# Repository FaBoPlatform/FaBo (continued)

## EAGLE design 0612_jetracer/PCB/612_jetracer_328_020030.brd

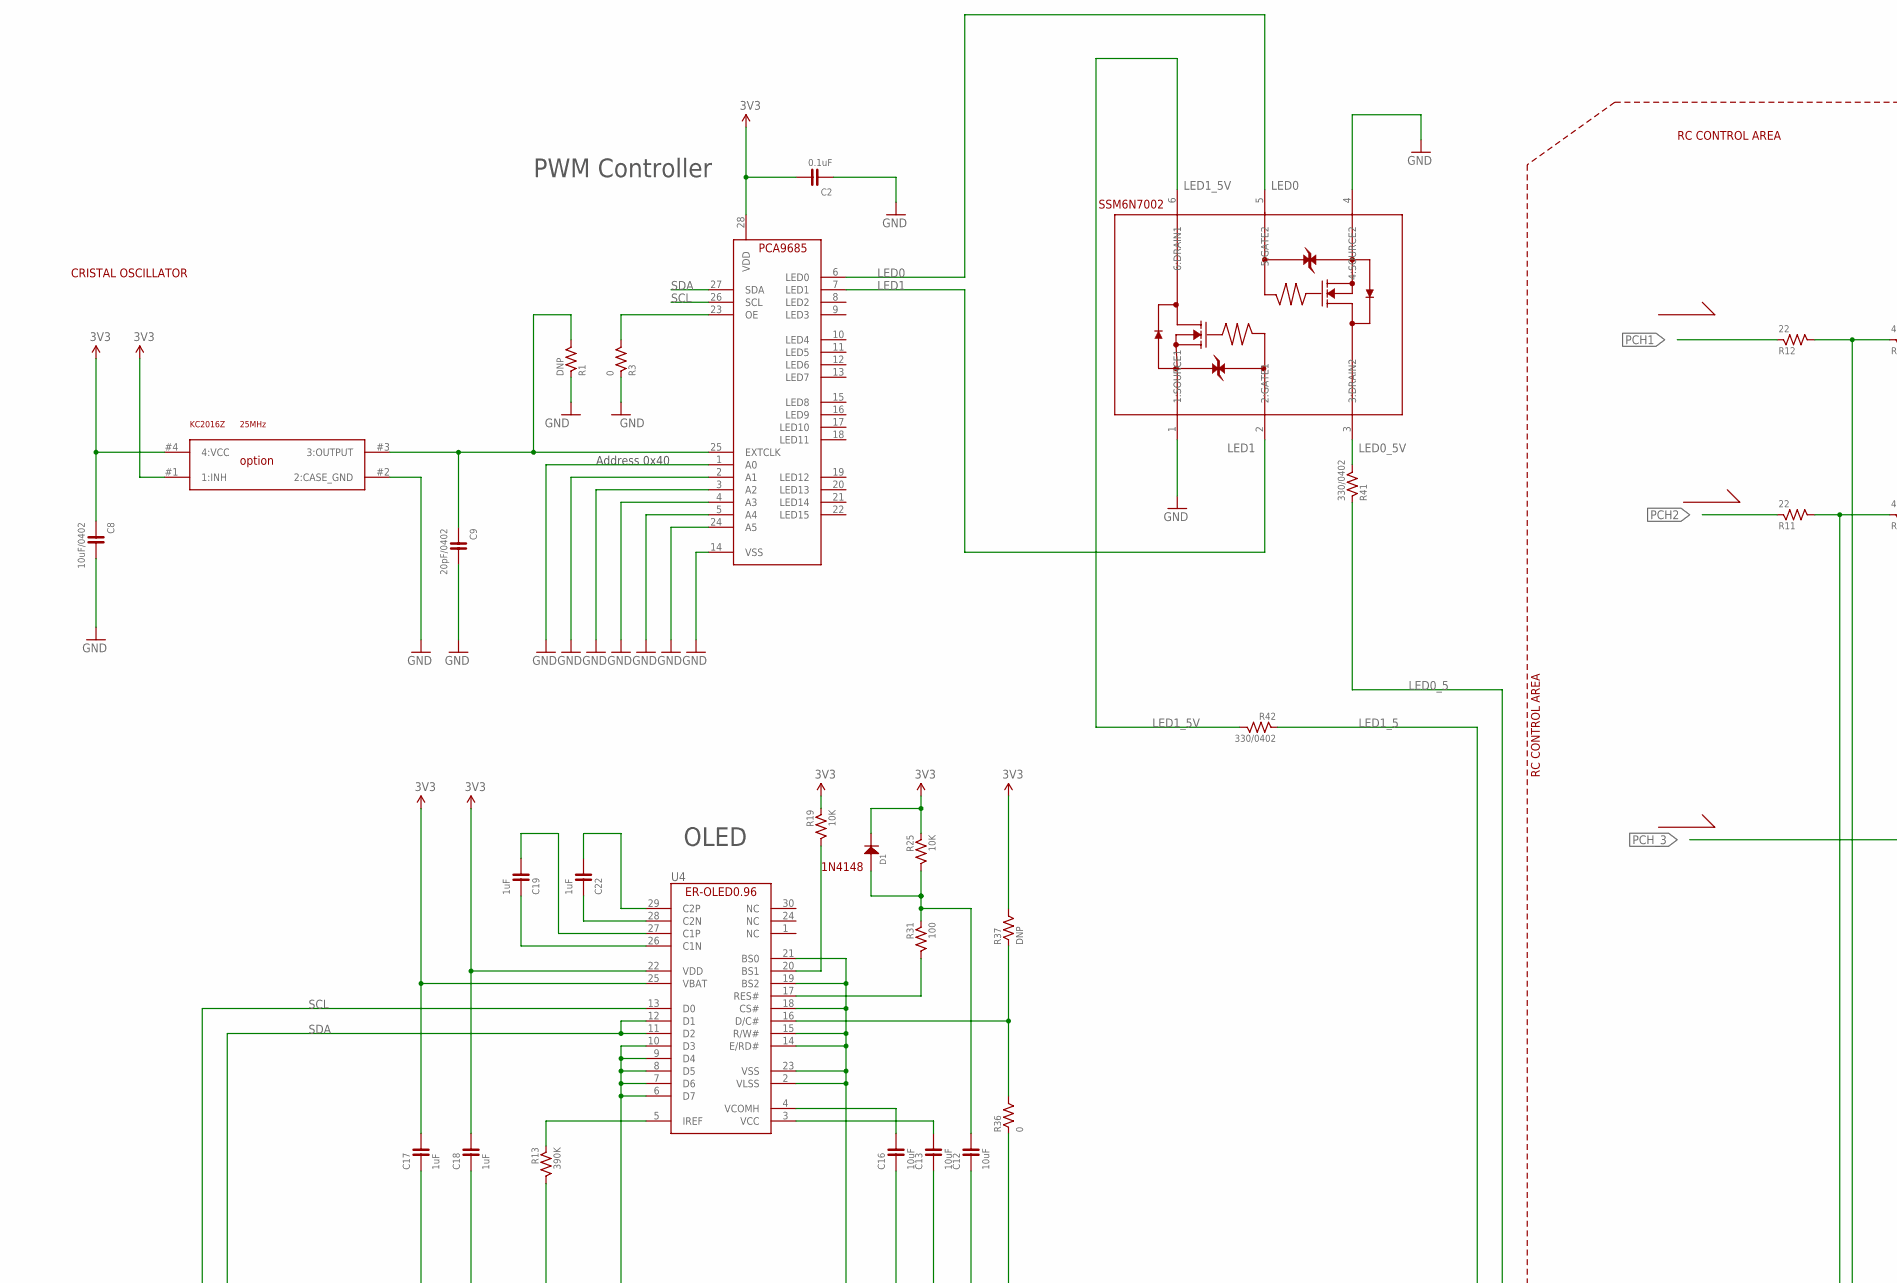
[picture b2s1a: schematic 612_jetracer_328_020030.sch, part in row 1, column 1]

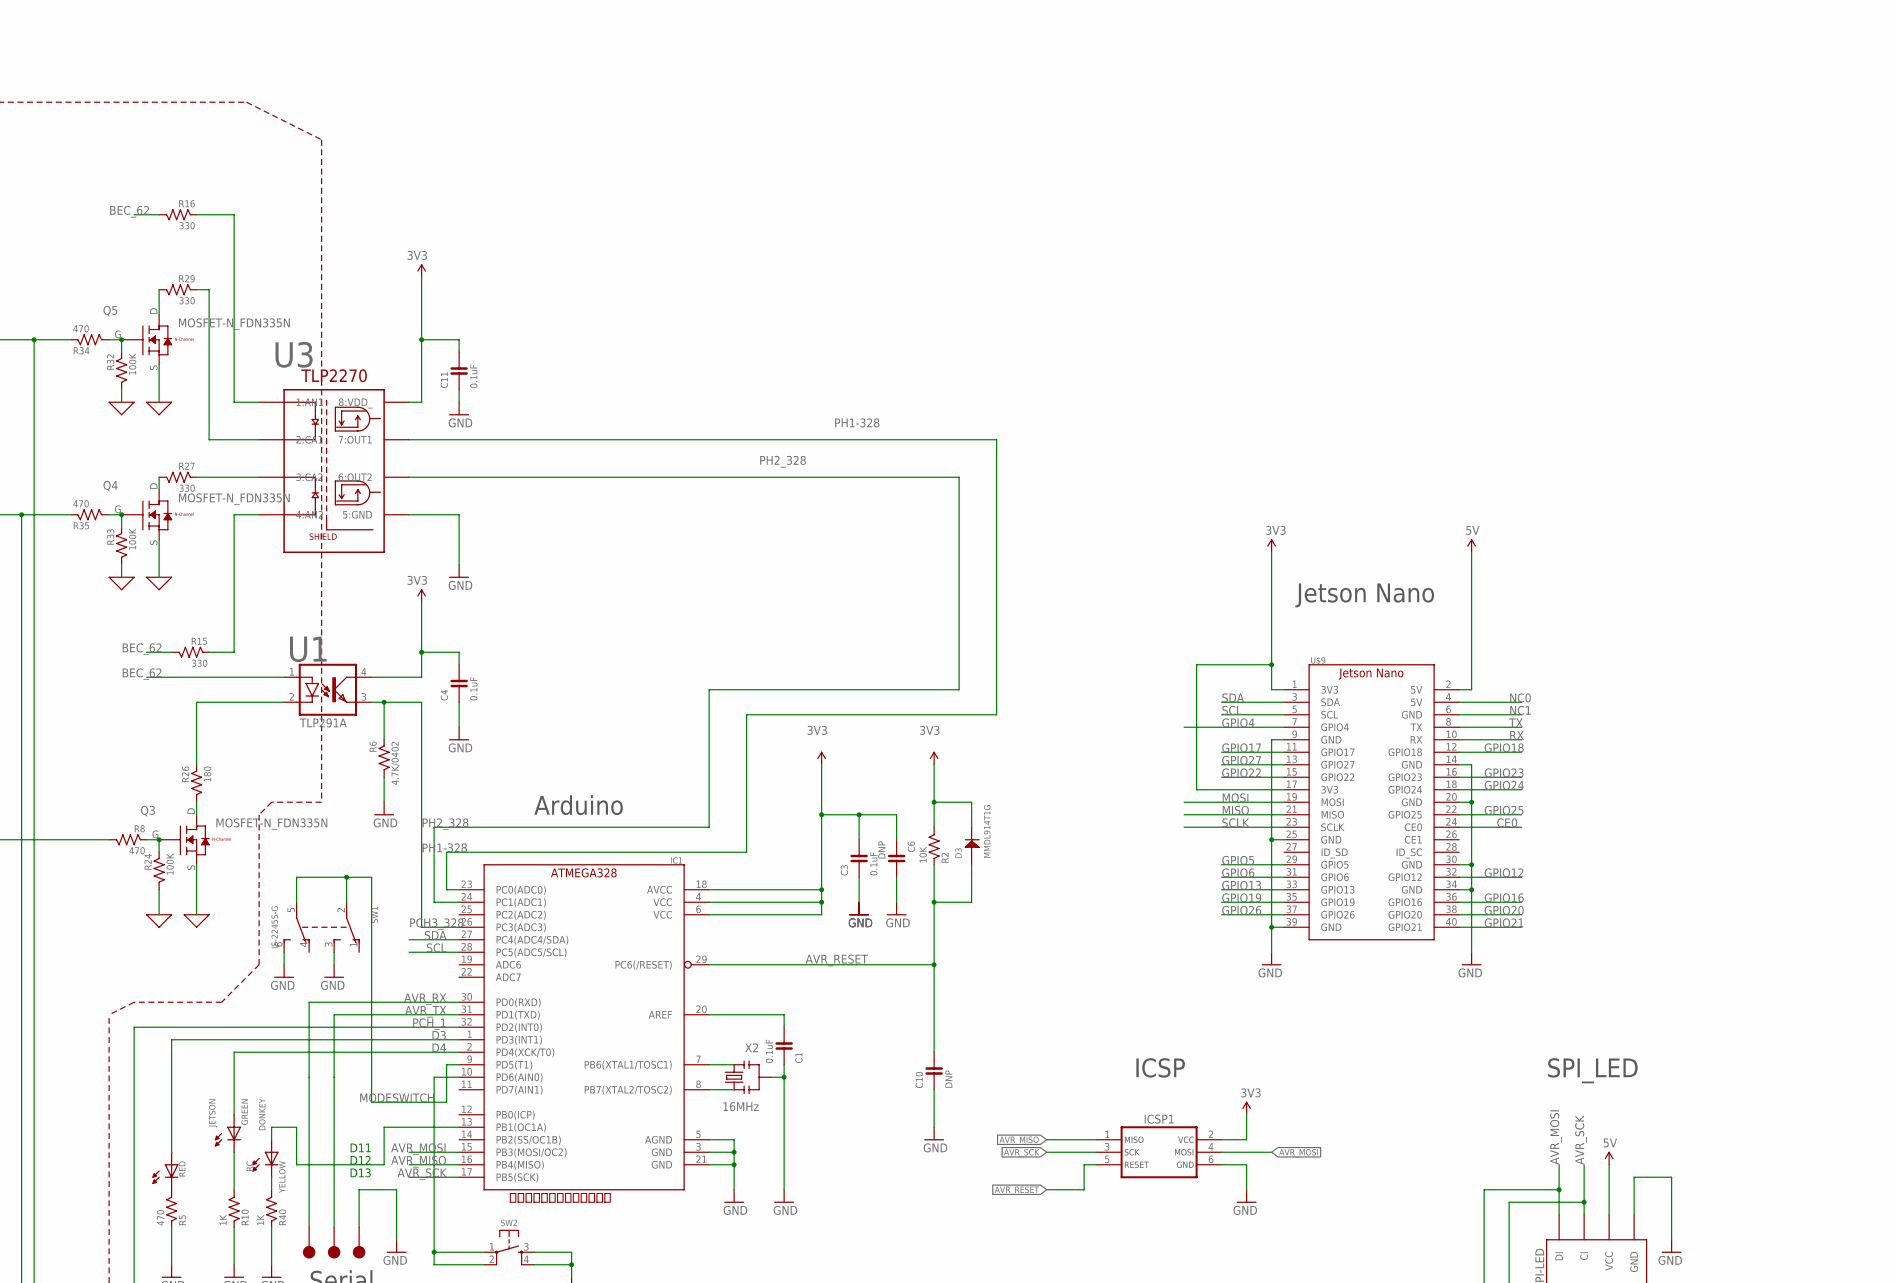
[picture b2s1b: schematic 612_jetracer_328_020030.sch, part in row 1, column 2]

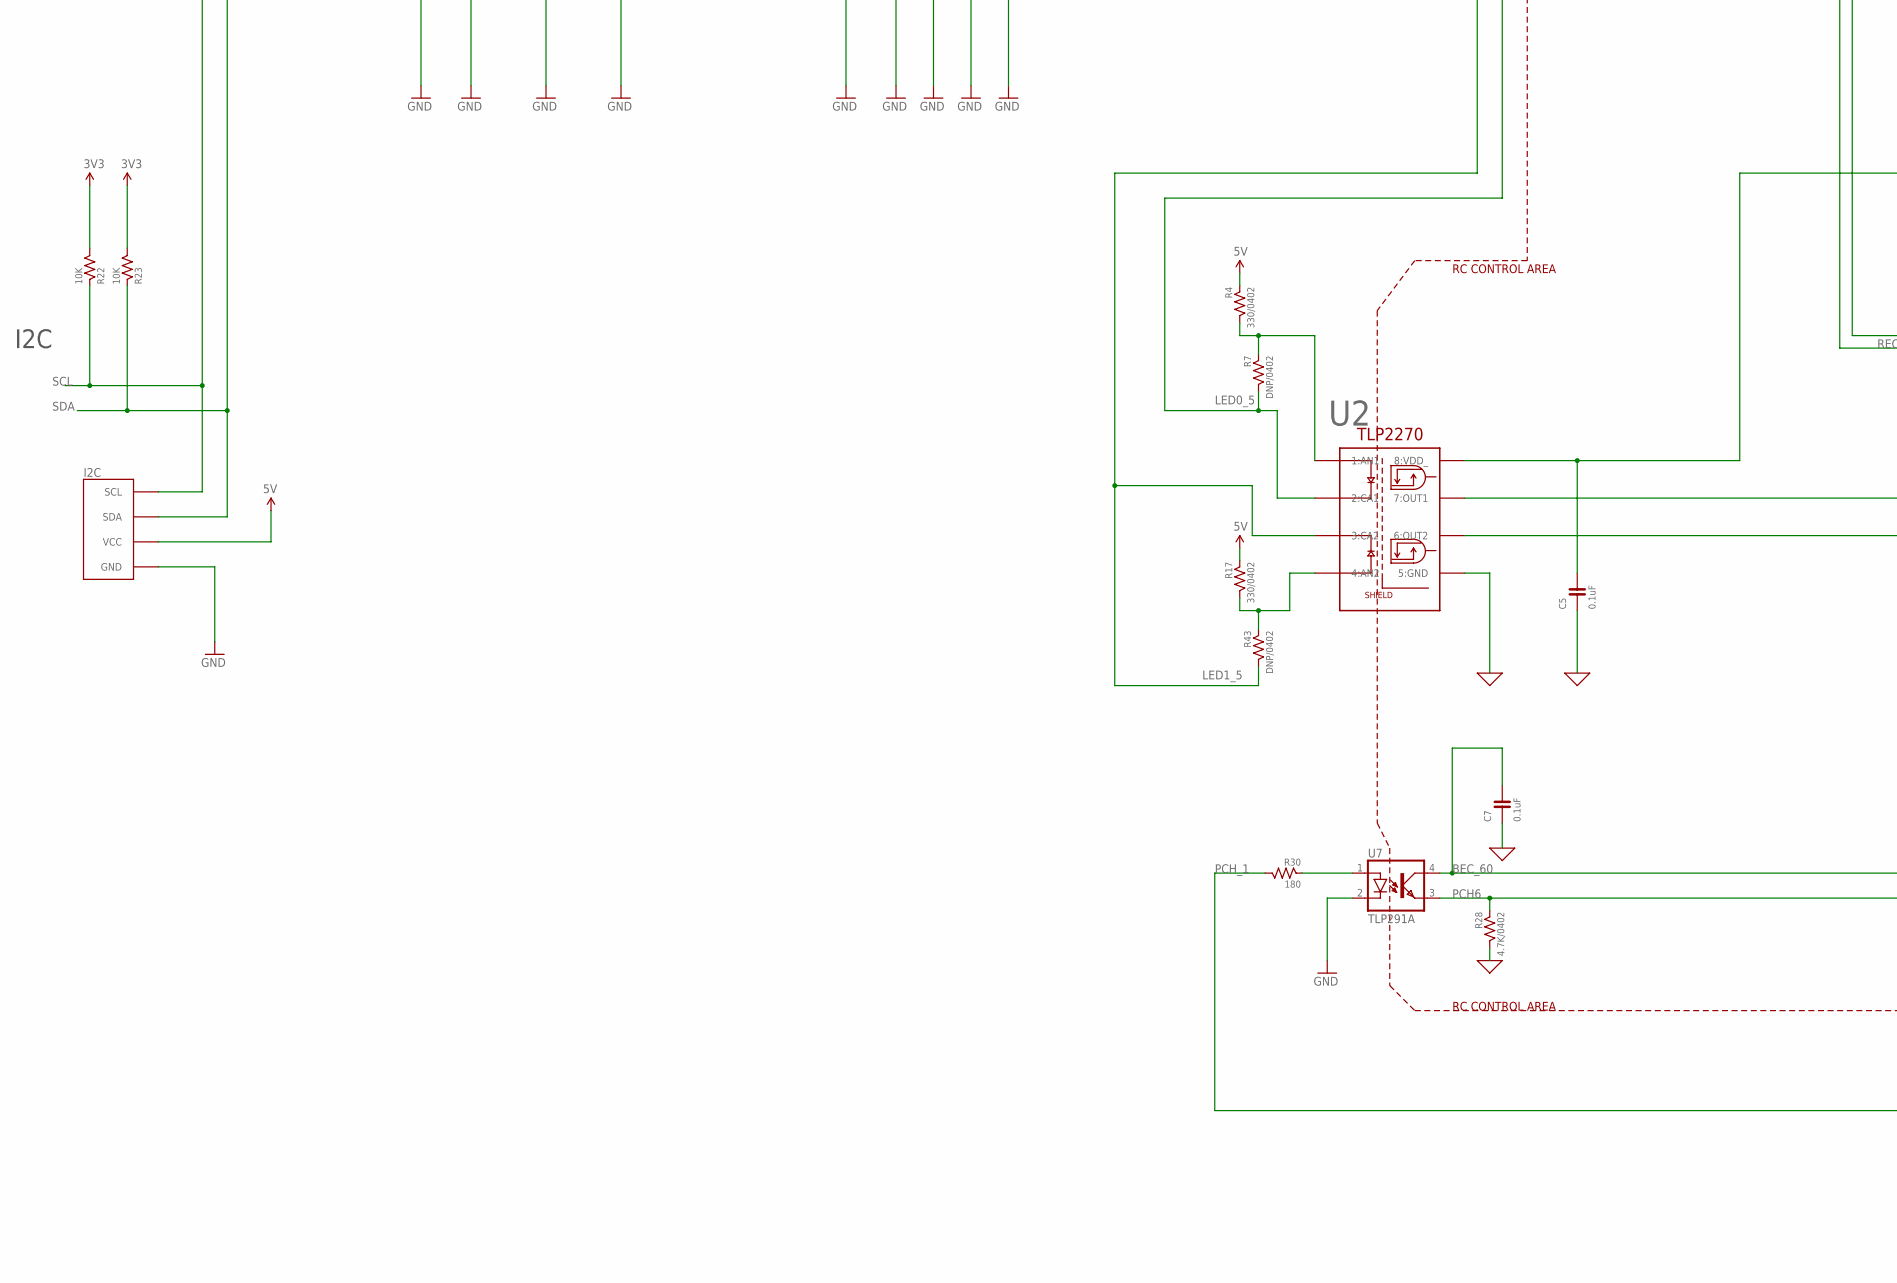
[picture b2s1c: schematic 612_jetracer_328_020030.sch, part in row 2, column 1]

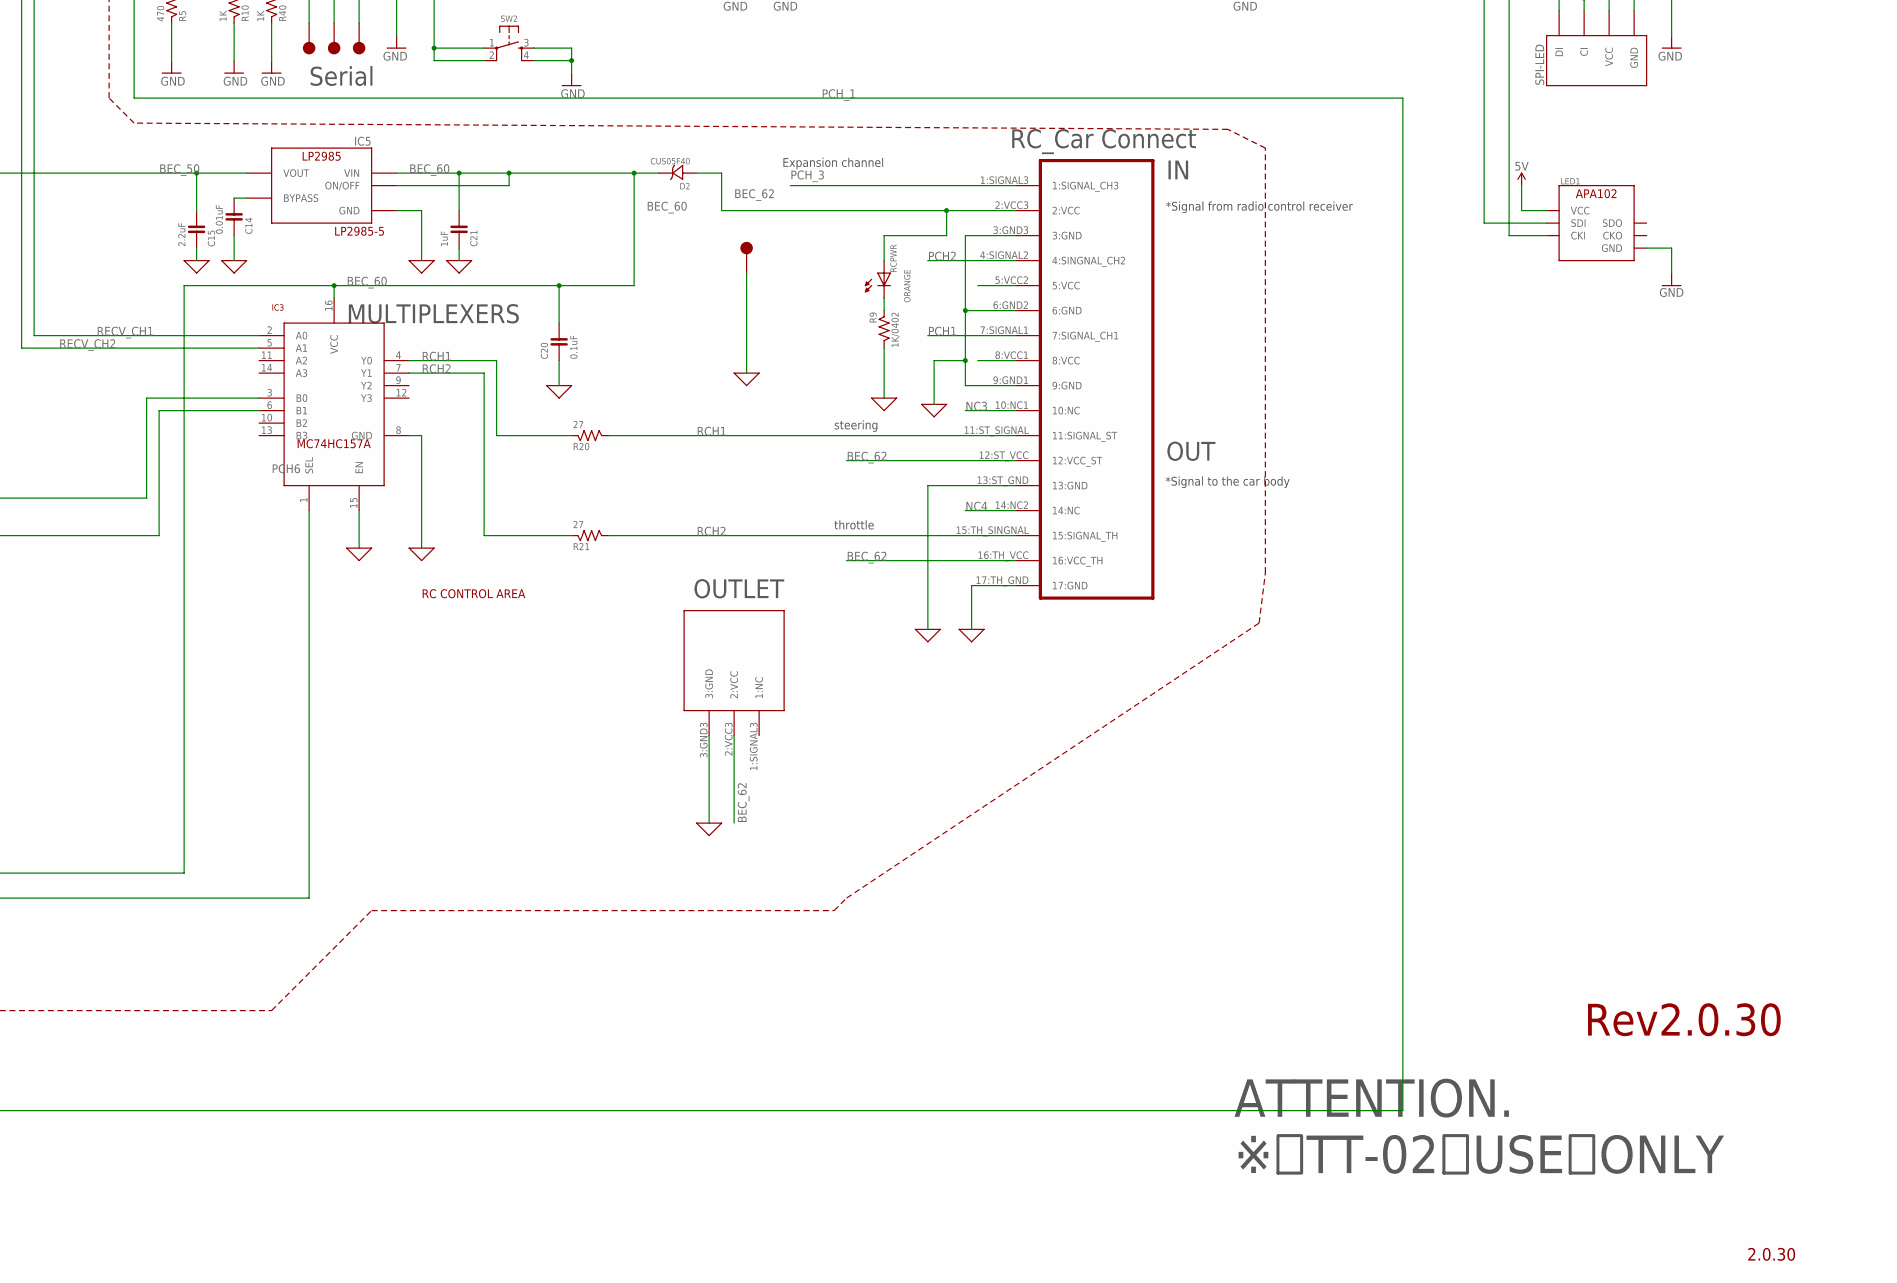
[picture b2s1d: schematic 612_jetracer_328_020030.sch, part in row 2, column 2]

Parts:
BEC62TP1: TP-15
C1, C2, C4, C11: 0.1uF; 0603
C3, C5, C7, C20: 0.1uF; 0402
C6: DNP; 0603
C8: 10uF/0402; 0402
C9: 20pF/0402; 0402
C10: DNP; 0402
C12, C13, C16: 10uF; 0603
C14: 0.01uF; 0603
C15: 2.2uF; 0603
C17, C18, C19, C21, C22: 1uF; 0603
D1: 1N4148; 1N4148W
D2: CUS05F40
D3: MMDL914T1G; SOD-323
DONKEY: YELLOW; 0603
I2C: FABO-I2C; I2C-SM04B-PASS-1-FL
IC1: ATMEGA328P-AU; TQFP-32
IC3: MULTIPLEXERSMC74HC157A; TSSOP-16
IC4: PCA9685_BOTTOM
IC5: LP2985-33DBV; SOT-23-5
ICSP1: ICSP_AVR-TC_NOHOLE; TC2030
JETSON: GREEN; 0603
LED1: APA102_IPIXEL; APA102_2020
Q3, Q4, Q5: MOSFET-N_FDN335N; SUPERSOT-3
R1: DNP; 0603
R2, R19, R22, R23, R25: 10K; 0603
R3: 0; 0603
R4, R17, R41, R42: 330/0402; 0402
R5, R8, R34, R35: 470; 0603
R6, R28: 4.7K/0402; 0402
R7, R43: DNP/0402; 0402
R9: 1K/0402; 0402
R10, R40: 1K; 0603
R11, R12: 22; 0603
R13: 390K; 0603
R15, R16, R27, R29: 330; 0603
R20, R21: 27; 0603
R24, R32, R33: 100K; 0603
R26, R30: 180; 0603
R31: 100; 0603
R36: 0; 0805
R37: DNP; 0805
RC: RED; 0603
RCPWR: ORANGE; 0603
SPI-LED: FABO-SPI-LED; SPI-SM04B-PASS-1-FL
SW1: IS-2245S-G
SW2: TACT-SWITCH-SMD_KMR2; KMR2
TP1, TP2, TP3: TP-15
U1, U7: TLP291A; 11-3C1
U2, U3: TLP2270
U4: ER-OLED0.96-1ER-CON30HT-1; ER-CON30HT-1
U$1: RC_17PIN_OUTIN; PNHEADER_2.54_SMT_17PIN_RC_TT01_02
U$3: RC_3PIN_POWEROUT; PNHEADER_2.54_SMT_3PIN_RC_TT01_02
U$9: JETSON_NANOJETSON_NANO_OVERALL; JETSON_NANO_DEMENTION
U$10: SSM6N7002KFU; US6
U$11: KC2016Z
X2: 16MHz; CSTNE_V_C

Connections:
0: BEC62TP1.1, C5.P$1 (1), C7.P$1 (1), C14.1, C15.1, C20.P$1 (1), C21.1, IC3.8 (GND), IC3.15 (EN), IC5.2 (GND), Q3.S, Q4.S, Q5.S, R9.2, R24.2, R28.2, R32.2, R33.2, U2.5 (5:GND), U$1.3:GND3 (3:GND), U$1.6:GND2 (6:GND), U$1.9:GND1 (9:GND), U$1.13:ST_GND (13:GND), U$1.17:TH_GND (17:GND), U$3.3:GND3 (3:GND)
3V3: C2.2, C3.P$2 (2), C4.2, C6.1, C8.P$1 (1), C11.2, C17.2, C18.2, D1.CATHODE, D3.K (CATHODE), IC1.4 (VCC), IC1.6 (VCC), IC1.18 (AVCC), IC4.28 (VDD), ICSP1.2, R2.2, R19.1, R22.2, R23.2, R25.1, R37.2, U1.4 (COL), U3.8 (8:VDD_), U4.22 (VDD), U4.25 (VBAT), U$9.1 (3V3), U$9.17 (3V3), U$11.#1 (1:INH), U$11.#4 (4:VCC)
5V: I2C.5V (VCC), LED1.VCC, R4.1, R17.1, SPI-LED.5V (VCC), U$9.2 (5V)
AVR_MISO: IC1.16 (PB4(MISO)), ICSP1.1
AVR_MOSI: IC1.15 (PB3(MOSI/OC2)), ICSP1.4, LED1.SDI, SPI-LED.DI
AVR_RESET: C10.P$2 (2), D3.A (ANODE), IC1.29 (PC6(/RESET)), ICSP1.5, R2.1
AVR_RX: IC1.30 (PD0(RXD)), TP1.1
AVR_SCK: IC1.17 (PB5(SCK)), ICSP1.3, LED1.CKI, SPI-LED.CI
AVR_TX: IC1.31 (PD1(TXD)), TP2.1
BEC_50: C5.P$2 (2), C15.2, IC5.5 (VOUT), U2.8 (8:VDD_)
BEC_60: C7.P$2 (2), C20.P$2 (2), C21.2, D2.C (CATHODE), IC3.16 (VCC), IC5.1 (VIN), IC5.3 (ON/OFF), U7.4 (COL)
BEC_62: D2.A (ANODE), R15.2, R16.2, RCPWR.ANODE, U1.1 (A), U$1.2:VCC3 (2:VCC), U$1.5:VCC2 (5:VCC), U$1.8:VCC1 (8:VCC), U$1.12:ST_VCC (12:VCC_ST), U$1.16:TH_VCC (16:VCC_TH), U$3.2:VCC3 (2:VCC)
CE0: U$9.24 (CE0)
D3: IC1.1 (PD3(INT1)), RC.ANODE
D4: IC1.2 (PD4(XCK/T0)), JETSON.ANODE
GND: C1.1, C2.1, C3.P$1 (1), C4.1, C6.2, C8.P$2 (2), C9.P$2 (2), C10.P$1 (1), C11.1, C12.1, C13.1, C16.1, C17.1, C18.1, I2C.GND, IC1.3 (GND), IC1.5 (AGND), IC1.21 (GND), IC4.1 (A0), IC4.2 (A1), IC4.3 (A2), IC4.4 (A3), IC4.5 (A4), IC4.14 (VSS), IC4.24 (A5), ICSP1.6, LED1.GND, R1.1, R3.1, R5.1, R6.2, R10.1, R13.2, R36.1, R40.1, SPI-LED.GND, SW1.3, SW1.6, SW2.3, SW2.4, TP3.1, U3.5 (5:GND), U4.2 (VLSS), U4.6 (D7), U4.7 (D6), U4.8 (D5), U4.9 (D4), U4.10 (D3), U4.14 (E/RD#), U4.15 (R/W#), U4.18 (CS#), U4.19 (BS2), U4.21 (BS0), U4.23 (VSS), U7.2 (C), U$9.9 (GND), U$9.14 (GND), U$9.20 (GND), U$9.25 (GND), U$9.30 (GND), U$9.34 (GND), U$9.39 (GND), U$10.1 (1:SOURCE1), U$10.4 (4:SOURCE2), U$11.#2 (2:CASE_GND), X2.2
GPIO4: U$9.7 (GPIO4)
GPIO5: U$9.29 (GPIO5)
GPIO6: U$9.31 (GPIO6)
GPIO12: U$9.32 (GPIO12)
GPIO13: U$9.33 (GPIO13)
GPIO16: U$9.36 (GPIO16)
GPIO17: U$9.11 (GPIO17)
GPIO18: U$9.12 (GPIO18)
GPIO19: U$9.35 (GPIO19)
GPIO20: U$9.38 (GPIO20)
GPIO21: U$9.40 (GPIO21)
GPIO22: U$9.15 (GPIO22)
GPIO23: U$9.16 (GPIO23)
GPIO24: U$9.18 (GPIO24)
GPIO25: U$9.22 (GPIO25)
GPIO26: U$9.37 (GPIO26)
GPIO27: U$9.13 (GPIO27)
LED0: IC4.6 (LED0), U$10.5 (5:GATE2)
LED0_5: R7.2, R41.1, U2.2 (2:CA1)
LED0_5V: R41.2, U$10.3 (3:DRAIN2)
LED1: IC4.7 (LED1), U$10.2 (2:GATE1)
LED1_5: R42.1, R43.2, U2.3 (3:CA2)
LED1_5V: R42.2, U$10.6 (6:DRAIN1)
MISO: U$9.21 (MISO)
MODESWITCH: IC1.9 (PD5(T1)), SW1.2, SW1.5
MOSI: U$9.19 (MOSI)
unnamed: R4.2, R7.1, U2.1 (1:AN1)
unnamed: C22.2, U4.29 (C2P)
unnamed: C1.2, IC1.20 (AREF)
unnamed: IC1.8 (PB7(XTAL2/TOSC2)), X2.3
unnamed: R26.1, U1.2 (C)
unnamed: IC4.23 (OE), R3.2
unnamed: DONKEY.ANODE, IC1.13 (PB1(OC1A))
unnamed: R15.1, U3.4 (4:AN2)
unnamed: IC3.3 (B0), U2.7 (7:OUT1)
unnamed: IC3.6 (B1), U2.6 (6:OUT2)
unnamed: R16.1, U3.1 (1:AN1)
unnamed: R17.2, R43.1, U2.4 (4:AN2)
unnamed: R13.1, U4.5 (IREF)
unnamed: IC1.7 (PB6(XTAL1/TOSC1)), X2.1
unnamed: C19.2, U4.27 (C1P)
unnamed: C13.2, U4.3 (VCC)
unnamed: R31.2, U4.17 (RES#)
unnamed: R5.2, RC.CATHODE
unnamed: JETSON.CATHODE, R10.2
unnamed: C19.1, U4.26 (C1N)
unnamed: C22.1, U4.28 (C2N)
unnamed: Q3.G, R8.1, R24.1
unnamed: R9.1, RCPWR.CATHODE
unnamed: C16.2, U4.4 (VCOMH)
unnamed: Q3.D, R26.2
unnamed: Q4.D, R27.2
unnamed: R27.1, U3.3 (3:CA2)
unnamed: Q5.D, R29.2
unnamed: R29.1, U3.2 (2:CA1)
unnamed: C14.2, IC5.4 (BYPASS)
unnamed: C12.2, D1.ANODE, R25.2, R31.1
unnamed: Q5.G, R32.1, R34.2
unnamed: R21.2, U$1.15:TH_SINGNAL (15:SIGNAL_TH)
unnamed: R20.2, U$1.11:ST_SIGNAL (11:SIGNAL_ST)
unnamed: R36.2, R37.1, U4.16 (D/C#)
unnamed: Q4.G, R33.1, R35.2
unnamed: C9.P$1 (1), IC4.25 (EXTCLK), R1.2, U$11.#3 (3:OUTPUT)
unnamed: R30.1, U7.1 (A)
unnamed: DONKEY.CATHODE, R40.2
unnamed: R19.2, U4.20 (BS1)
NC0: U$9.4 (5V)
NC1: U$9.6 (GND)
NC3: U$1.10:NC1 (10:NC)
NC4: U$1.14:NC2 (14:NC)
PCH1: R12.1, U$1.7:SIGNAL1 (7:SIGNAL_CH1)
PCH2: R11.1, U$1.4:SIGNAL2 (4:SINGNAL_CH2)
PCH3_328: IC1.26 (PC3(ADC3)), R6.1, U1.3 (EMI)
PCH6: IC3.1 (SEL), R28.1, U7.3 (EMI)
PCH_1: IC1.32 (PD2(INT0)), R30.2
PCH_3: R8.2, U$1.1:SIGNAL3 (1:SIGNAL_CH3)
PH1-328: IC1.23 (PC0(ADC0)), U3.7 (7:OUT1)
PH2_328: IC1.24 (PC1(ADC1)), U3.6 (6:OUT2)
RCH1: IC3.4 (Y0), R20.1
RCH2: IC3.7 (Y1), R21.1
RECV_CH1: IC3.2 (A0), R12.2, R34.1
RECV_CH2: IC3.5 (A1), R11.2, R35.1
RX: U$9.10 (RX)
SCL: I2C.SCL, IC1.28 (PC5(ADC5/SCL)), IC4.26 (SCL), R22.1, U4.13 (D0), U$9.5 (SCL)
SCLK: U$9.23 (SCLK)
SDA: I2C.SDA, IC1.27 (PC4(ADC4/SDA)), IC4.27 (SDA), R23.1, U4.11 (D2), U4.12 (D1), U$9.3 (SDA)
SW: IC1.10 (PD6(AIN0)), SW2.1, SW2.2
TX: U$9.8 (TX)

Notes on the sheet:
2.0.30
Jetson Nano
PWM Controller
Address 0x40
MULTIPLEXERS
D11
D12
D13
Arduino
Serial
ICSP
*Signal from radio control receiver
*Signal to the car body
steering
throttle
Expansion channel
OUT
SPI_LED
MC74HC157A
RC CONTROL AREA
LP2985-5
ATTENTION. ※ TT-02 USE ONLY
ＡＴＭＥＧＡ３２８Ｐ－ＡＵ
RC_Car Connect
option
CRISTAL OSCILLATOR
I2C
OUTLET
1N4148
OLED
Rev2.0.30

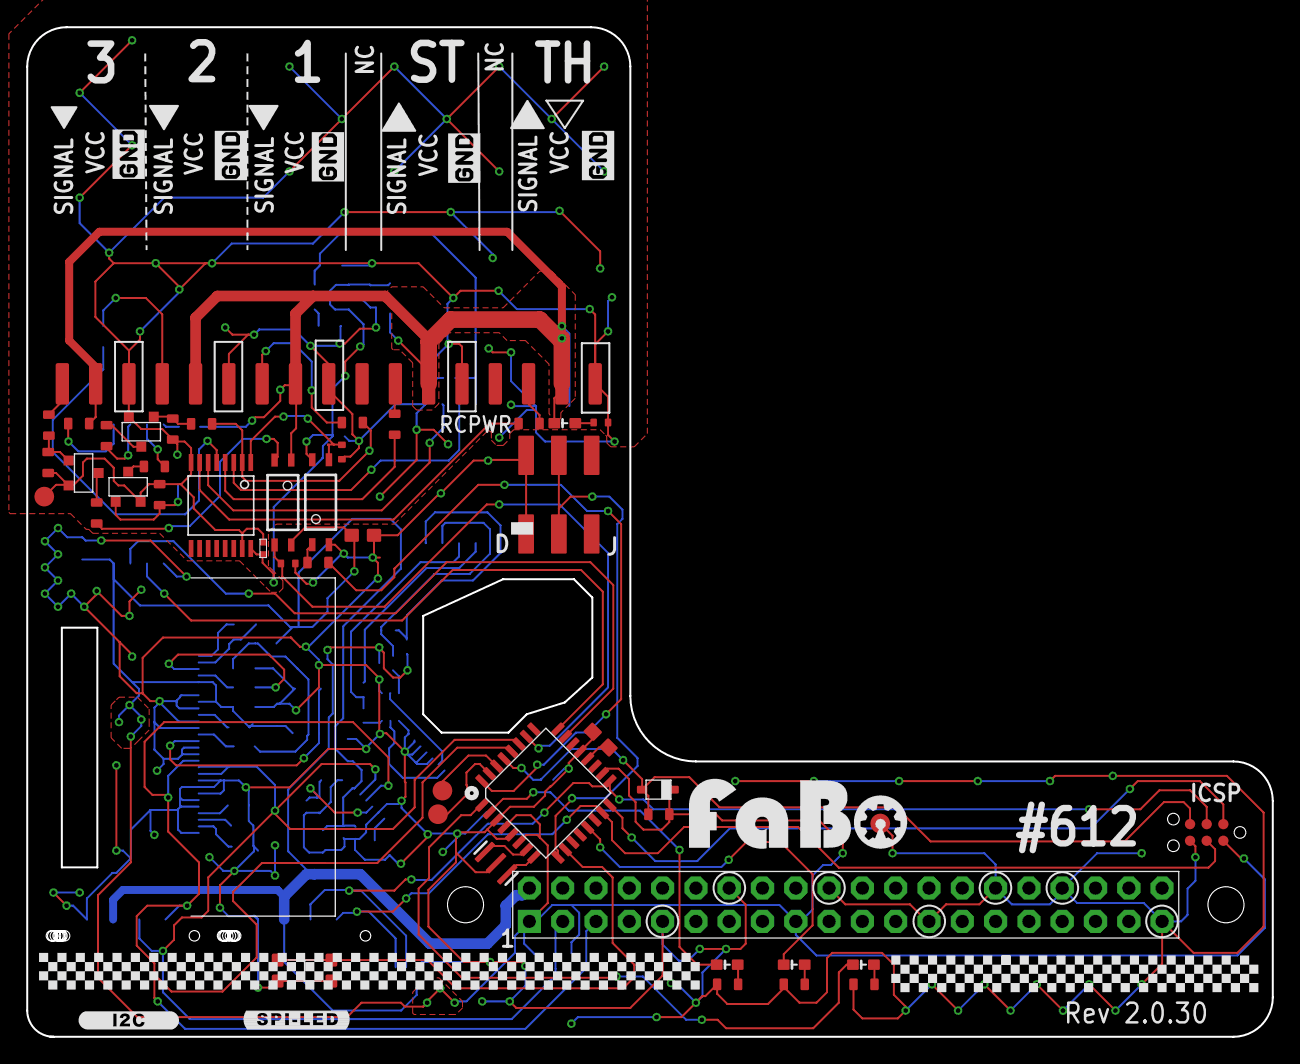
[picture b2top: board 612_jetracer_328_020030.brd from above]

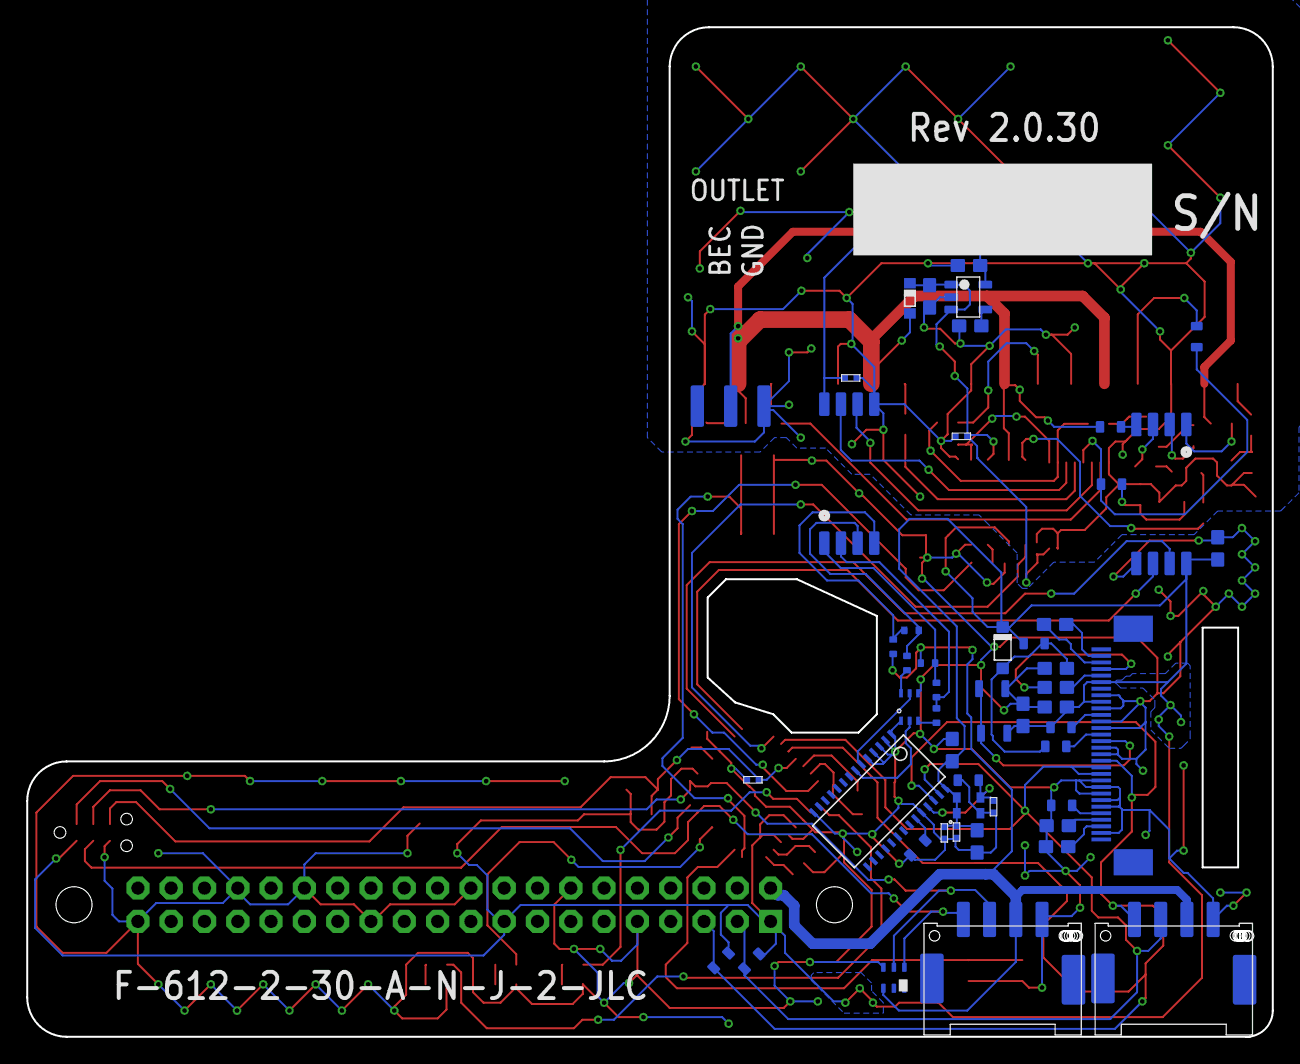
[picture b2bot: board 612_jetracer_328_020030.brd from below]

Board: 2 copper layers, 95.0 x 77.0 mm, 102 parts (49 on the bottom side), 77 nets.

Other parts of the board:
U$2: LOGO_FABO_L
U$5, U$6, U$7, U$8, U$12: LOGO_SILK_GND

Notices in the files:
parts and their libraries:
FaBo-etc: Released under the Creative Commons Attribution-ShareAlike 4.0 License
https://creativecommons.org/licenses/by-sa/4.0
